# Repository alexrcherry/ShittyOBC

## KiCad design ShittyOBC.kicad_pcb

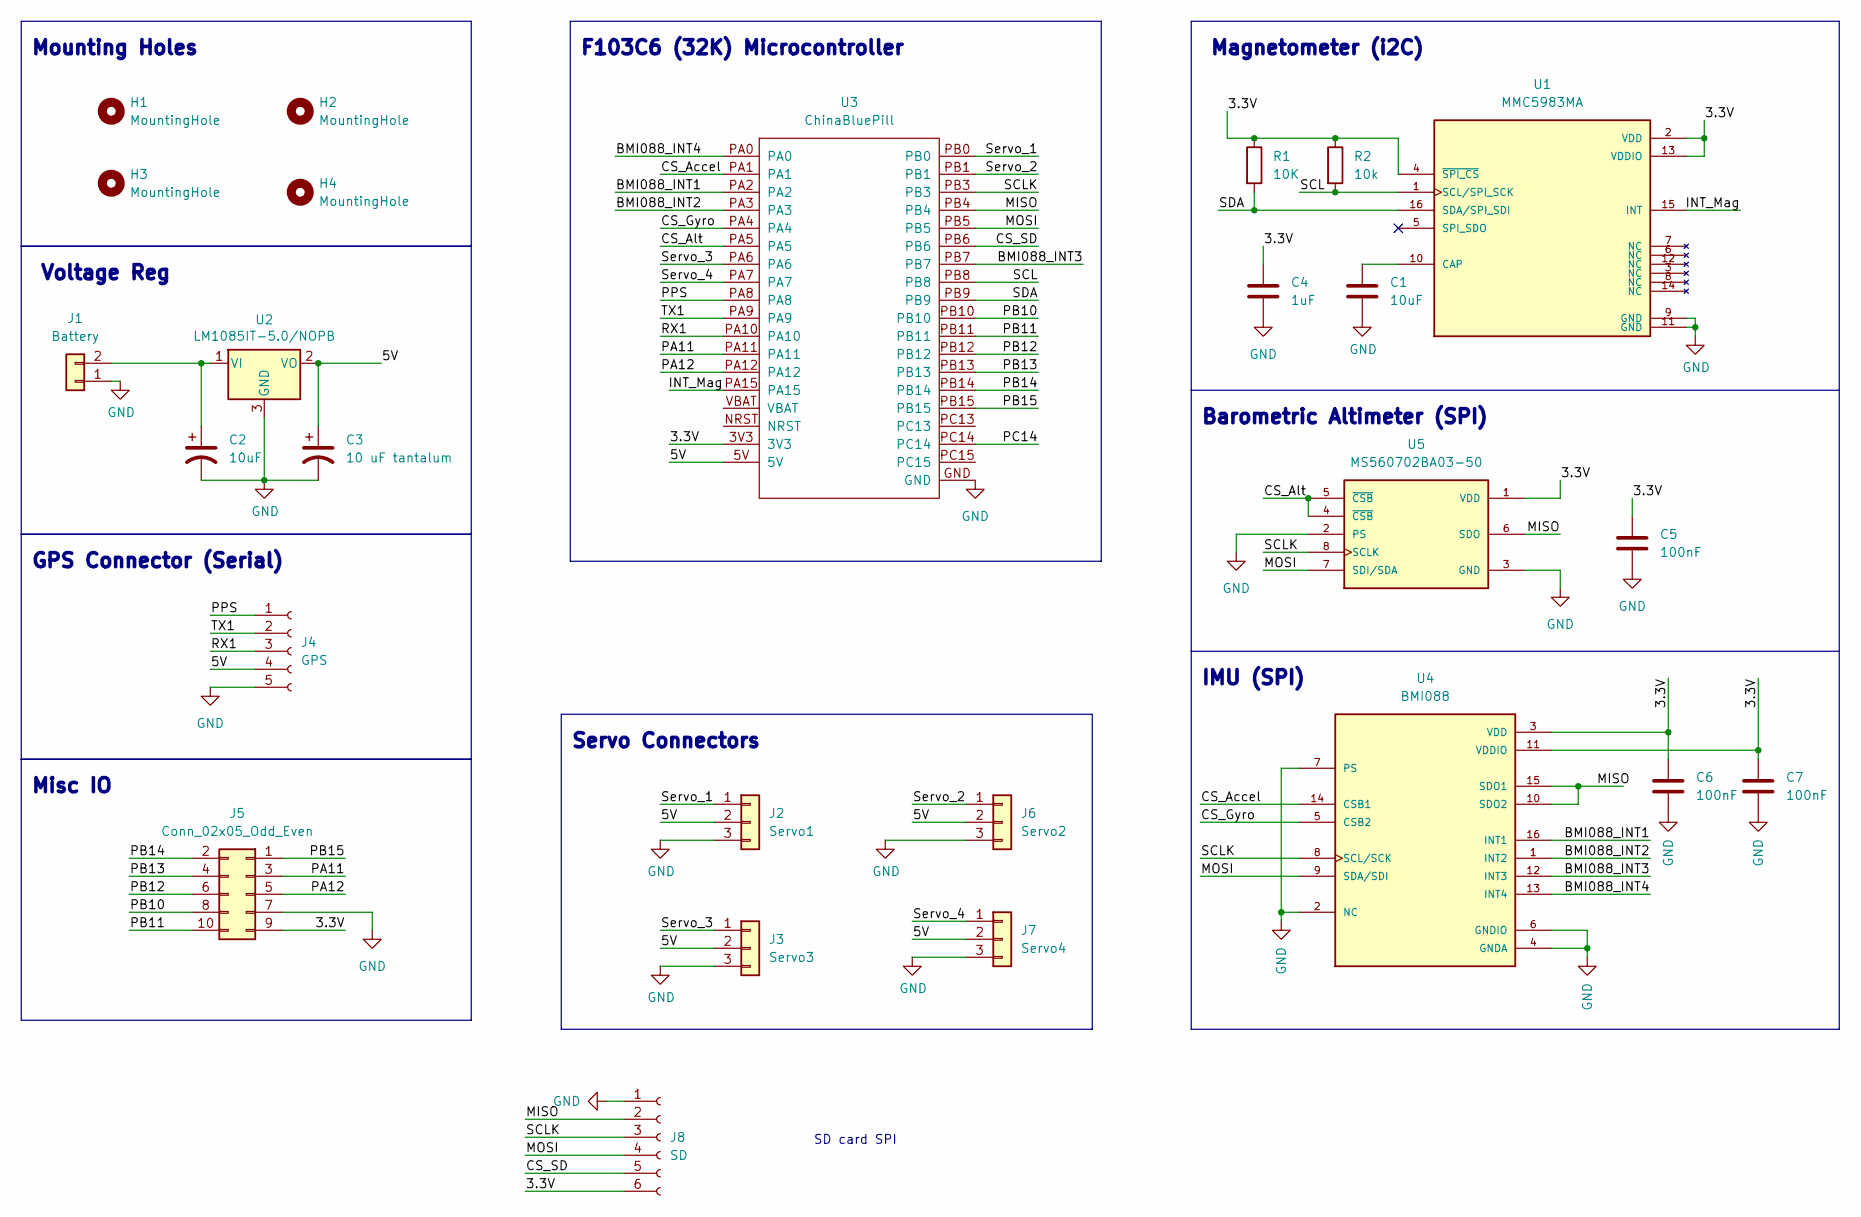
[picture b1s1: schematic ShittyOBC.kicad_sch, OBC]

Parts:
C1, C2: 10uF; C_0603_1608Metric
C3: 10 uF tantalum; C_0603_1608Metric
C4: 1uF; C_0603_1608Metric
C5, C6, C7: 100nF; C_0603_1608Metric
H1, H2, H3, H4: MountingHole; MountingHole_3.2mm_M3
J1: Battery; AMASS_XT60-M_1x02_P7.20mm_Vertical
J2: Servo1; PinHeader_1x03_P2.54mm_Vertical
J3: Servo3; PinHeader_1x03_P2.54mm_Vertical
J4: GPS; JST_EH_B5B-EH-A_1x05_P2.50mm_Vertical
J5: Conn_02x05_Odd_Even; PinSocket_2x05_P2.54mm_Vertical
J6: Servo2; PinHeader_1x03_P2.54mm_Vertical
J7: Servo4; PinHeader_1x03_P2.54mm_Vertical
J8: SD; PinSocket_1x06_P2.54mm_Vertical
R1: 10K; R_0402_1005Metric
R2: 10k; R_0402_1005Metric
U1: MMC5983MA; PQFN50P300X300X100-16N; PARTREV A
U2: LM1085IT-5.0/NOPB; TO-220-3_Vertical
U3: ChinaBluePill
U4: BMI088; PQFN50P450X300X100-16N
U5: MS560702BA03-50; SON125P300X500X100-8N

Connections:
/3.3V: C4.1, C5.1, C6.1, C7.1, J5.9, J8.6, R1.1, R2.1, U1.2 (VDD), U1.4 (~SPI_CS), U1.13 (VDDIO), U3.3V3, U4.3 (VDD), U4.11 (VDDIO), U5.1 (VDD)
/5V: C3.1, J2.2, J3.2, J4.4, J6.2, J7.2, U2.2 (VO), U3.5V
/BMI088_INT1: U3.PA2, U4.16 (INT1)
/BMI088_INT2: U3.PA3, U4.1 (INT2)
/BMI088_INT3: U3.PB7, U4.12 (INT3)
/BMI088_INT4: U3.PA0, U4.13 (INT4)
/CS_Accel: U3.PA1, U4.14 (CSB1)
/CS_Alt: U3.PA5, U5.4 (~CSB), U5.5 (~CSB)
/CS_Gyro: U3.PA4, U4.5 (CSB2)
/CS_SD: J8.5, U3.PB6
/INT_Mag: U1.15 (INT), U3.PA15
/MISO: J8.2, U3.PB4, U4.10 (SDO2), U4.15 (SDO1), U5.6 (SDO)
/MOSI: J8.4, U3.PB5, U4.9 (SDA/SDI), U5.7 (SDI/SDA)
/PA11: J5.3, U3.PA11
/PA12: J5.5, U3.PA12
/PB10: J5.8, U3.PB10
/PB11: J5.10, U3.PB11
/PB12: J5.6, U3.PB12
/PB13: J5.4, U3.PB13
/PB14: J5.2, U3.PB14
/PB15: J5.1, U3.PB15
/PC14: U3.PC14
/PPS: J4.1, U3.PA8
/RX1: J4.3, U3.PA10
/SCL: R2.2, U1.1 (SCL/SPI_SCK), U3.PB8
/SCLK: J8.3, U3.PB3, U4.8 (SCL/SCK), U5.8 (SCLK)
/SDA: R1.2, U1.16 (SDA/SPI_SDI), U3.PB9
/Servo_1: J2.1, U3.PB0
/Servo_2: J6.1, U3.PB1
/Servo_3: J3.1, U3.PA6
/Servo_4: J7.1, U3.PA7
/TX1: J4.2, U3.PA9
GND: C1.2, C2.2, C3.2, C4.2, C5.2, C6.2, C7.2, J1.1, J2.3, J3.3, J4.5, J5.7, J6.3, J7.3, J8.1, U1.9 (GND), U1.11 (GND), U2.3 (GND), U3.GND, U4.2 (NC), U4.4 (GNDA), U4.6 (GNDIO), U4.7 (PS), U5.2 (PS), U5.3 (GND)
unnamed: C1.1, U1.10 (CAP)
unnamed: C2.1, J1.2, U2.1 (VI)

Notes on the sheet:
Mounting Holes
SD card SPI
Magnetometer (i2C)
IMU (SPI)
Voltage Reg
Servo Connectors
Misc IO
GPS Connector (Serial)
Barometric Altimeter (SPI)
F103C6 (32K) Microcontroller

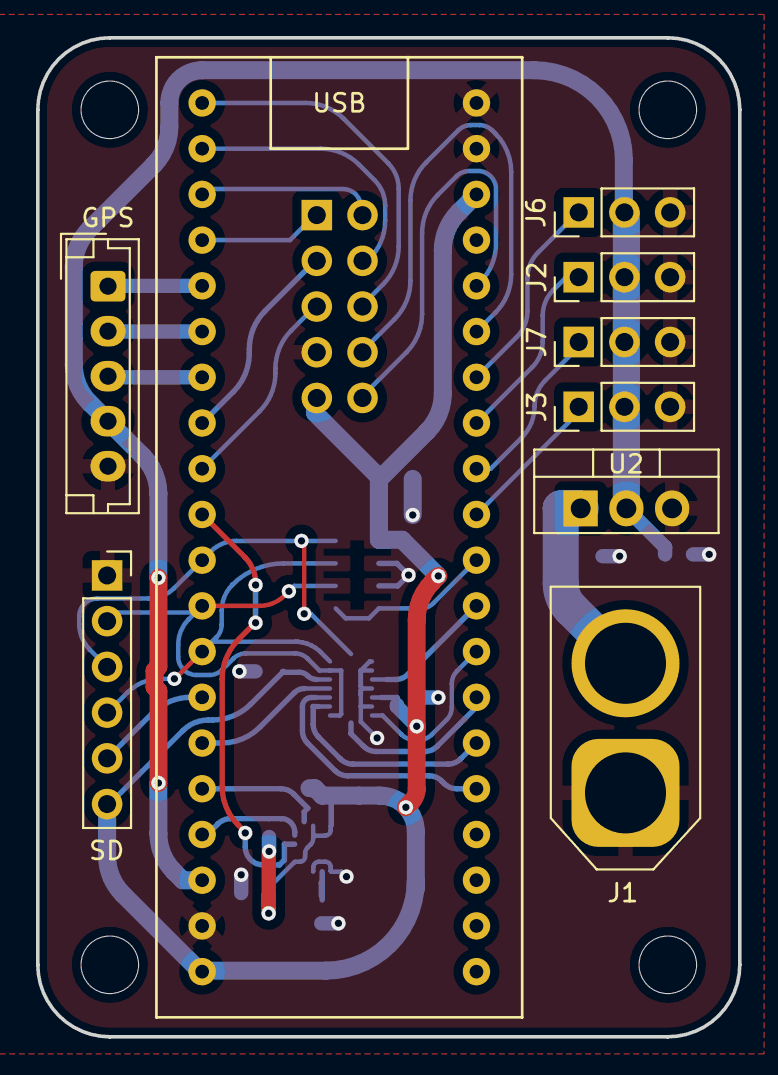
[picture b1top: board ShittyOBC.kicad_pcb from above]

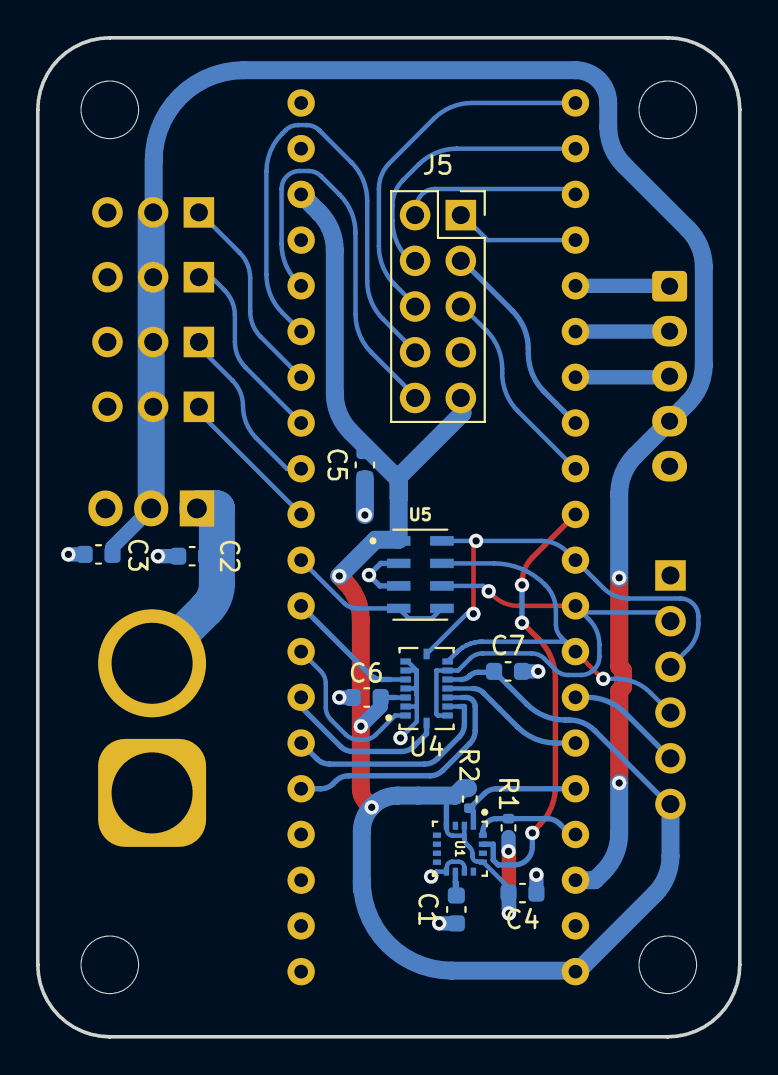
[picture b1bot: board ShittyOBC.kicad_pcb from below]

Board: 2 copper layers, 39.0 x 55.5 mm, 26 parts (13 on the bottom side), 34 nets.
